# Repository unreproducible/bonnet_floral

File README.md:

Floral Bonnet

This is an IoT-ish style Bonnet (Hat) intended for a Raspberry Pi Zero based board.

Obviously you can use it on anything with the appropriate header.

Includes:
* BME280 - I2C
* TSL2561 - I2C
* 128x64 OLED Screen - SPI
* RGB LED - 3xGPIO/PWM
* User Button - GPIO
* Serial Port for Kernel Debugging

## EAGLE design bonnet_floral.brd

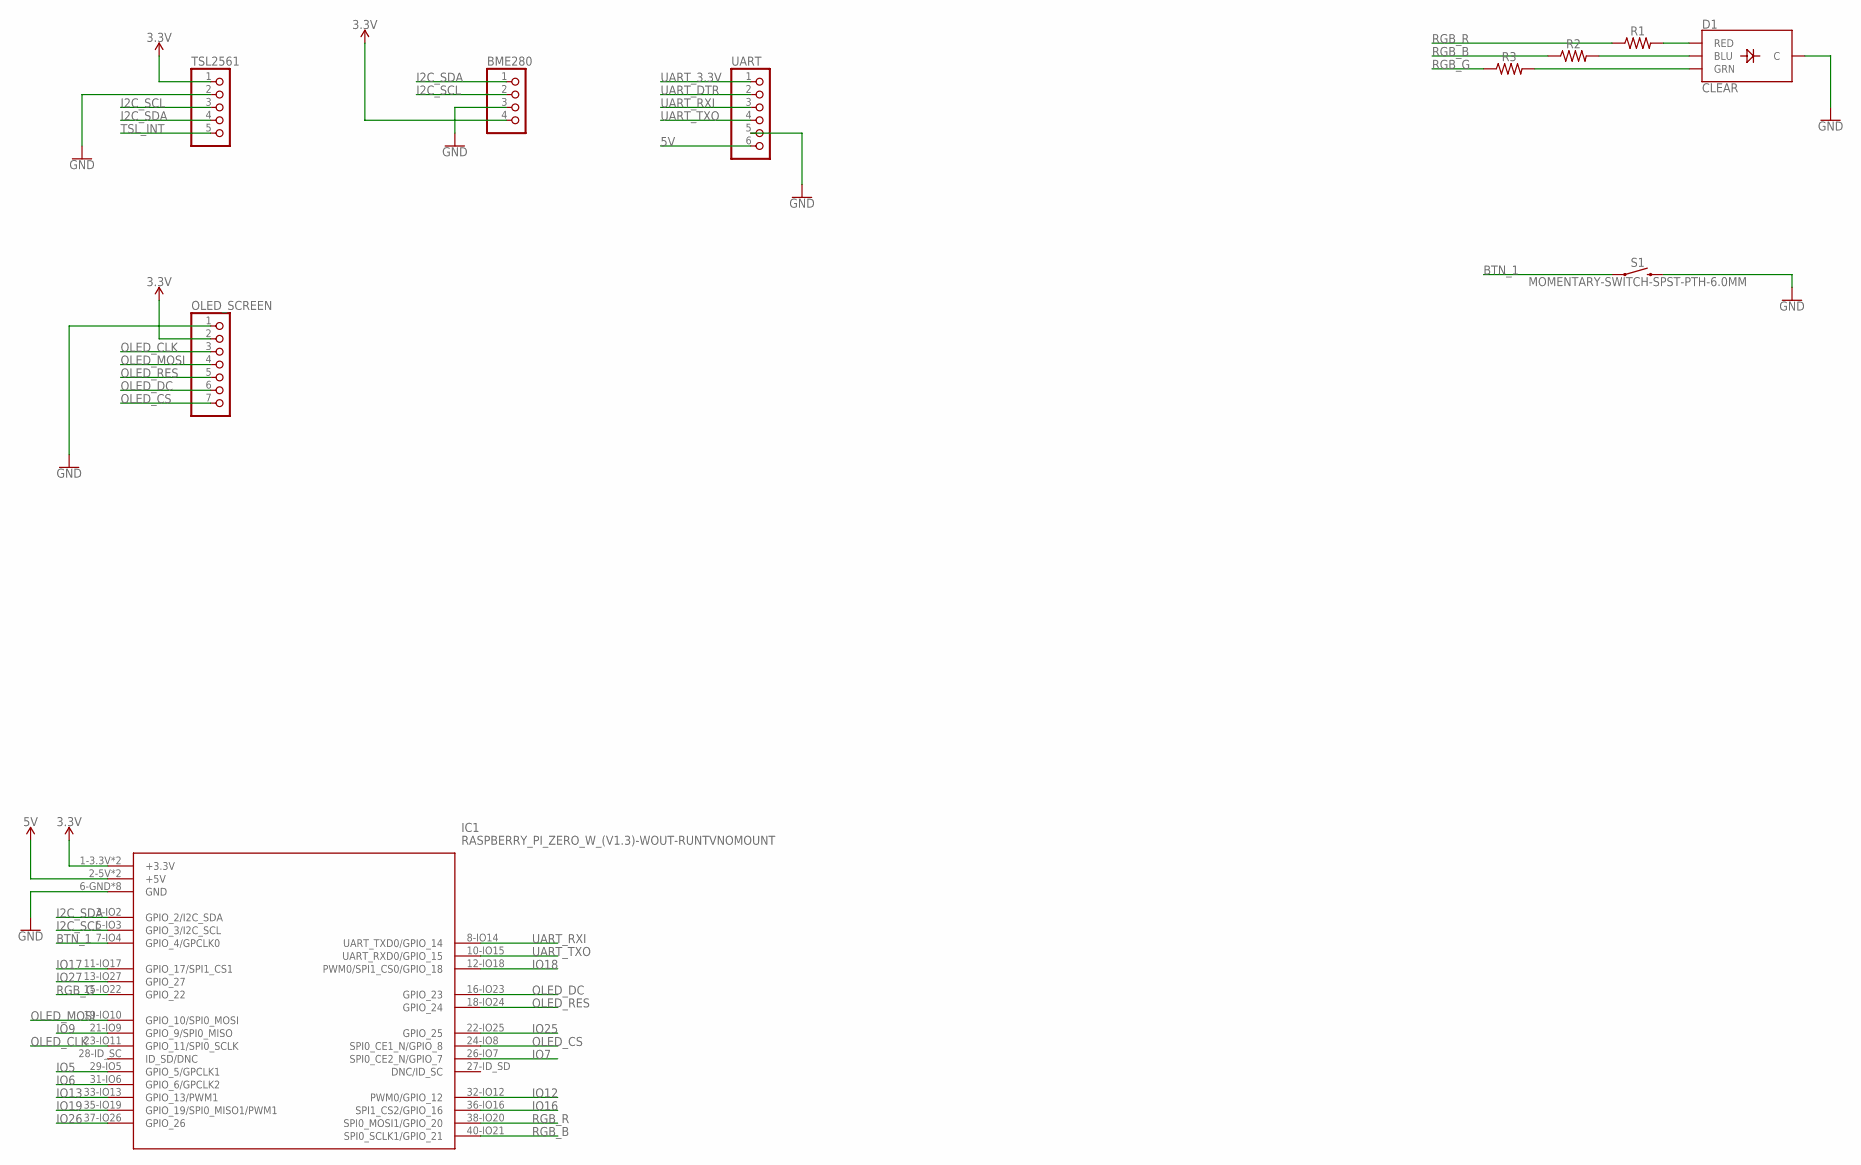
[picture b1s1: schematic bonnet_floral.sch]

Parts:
BME280: PINHD-1X4; 1X04
D1: CLEAR; LED-RGB-THRU@1
IC1: RASPBERRY_PI_ZERO_W_(V1.3)-WOUT-RUNTVNOMOUNT; RASPBERRYPIZEROWV13-WOUT-RUNTV-NOMOUNT
OLED_SCREEN: PINHD-1X7; 1X07
R1, R2, R3: AXIAL-0.3
S1: MOMENTARY-SWITCH-SPST-PTH-6.0MM; TACTILE_SWITCH_PTH_6.0MM
TSL2561: PINHD-1X5; 1X05
UART: PINHD-1X6; 1X06

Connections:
3.3V: BME280.4, IC1.1-3.3V (+3.3V), IC1.17-3.3V (+3.3V), OLED_SCREEN.2, TSL2561.1
5V: IC1.2-5V (+5V), IC1.4-5V (+5V), UART.6
BTN_1: IC1.7-IO4 (GPIO_4/GPCLK0), S1.1
GND: BME280.3, D1.2 (C), IC1.6-GND (GND), IC1.9-GND (GND), IC1.14-GND (GND), IC1.20-GND (GND), IC1.25-GND (GND), IC1.30-GND (GND), IC1.34-GND (GND), IC1.39-GND (GND), OLED_SCREEN.1, S1.3 (2), TSL2561.2, UART.5
I2C_SCL: BME280.2, IC1.5-IO3 (GPIO_3/I2C_SCL), TSL2561.3
I2C_SDA: BME280.1, IC1.3-IO2 (GPIO_2/I2C_SDA), TSL2561.4
IO5: IC1.29-IO5 (GPIO_5/GPCLK1)
IO6: IC1.31-IO6 (GPIO_6/GPCLK2)
IO7: IC1.26-IO7 (SPI0_CE2_N/GPIO_7)
IO9: IC1.21-IO9 (GPIO_9/SPI0_MISO)
IO12: IC1.32-IO12 (PWM0/GPIO_12)
IO13: IC1.33-IO13 (GPIO_13/PWM1)
IO16: IC1.36-IO16 (SPI1_CS2/GPIO_16)
IO17: IC1.11-IO17 (GPIO_17/SPI1_CS1)
IO18: IC1.12-IO18 (PWM0/SPI1_CS0/GPIO_18)
IO19: IC1.35-IO19 (GPIO_19/SPI0_MISO1/PWM1)
IO25: IC1.22-IO25 (GPIO_25)
IO26: IC1.37-IO26 (GPIO_26)
IO27: IC1.13-IO27 (GPIO_27)
unnamed: D1.1 (RED), R1.P$2 (2)
unnamed: D1.4 (BLU), R2.P$2 (2)
unnamed: D1.3 (GRN), R3.P$2 (2)
OLED_CLK: IC1.23-IO11 (GPIO_11/SPI0_SCLK), OLED_SCREEN.3
OLED_CS: IC1.24-IO8 (SPI0_CE1_N/GPIO_8), OLED_SCREEN.7
OLED_DC: IC1.16-IO23 (GPIO_23), OLED_SCREEN.6
OLED_MOSI: IC1.19-IO10 (GPIO_10/SPI0_MOSI), OLED_SCREEN.4
OLED_RES: IC1.18-IO24 (GPIO_24), OLED_SCREEN.5
RGB_B: IC1.40-IO21 (SPI0_SCLK1/GPIO_21), R2.P$1 (1)
RGB_G: IC1.15-IO22 (GPIO_22), R3.P$1 (1)
RGB_R: IC1.38-IO20 (SPI0_MOSI1/GPIO_20), R1.P$1 (1)
TSL_INT: TSL2561.5
UART_3.3V: UART.1
UART_DTR: UART.2
UART_RXI: IC1.8-IO14 (UART_TXD0/GPIO_14), UART.3
UART_TXO: IC1.10-IO15 (UART_RXD0/GPIO_15), UART.4

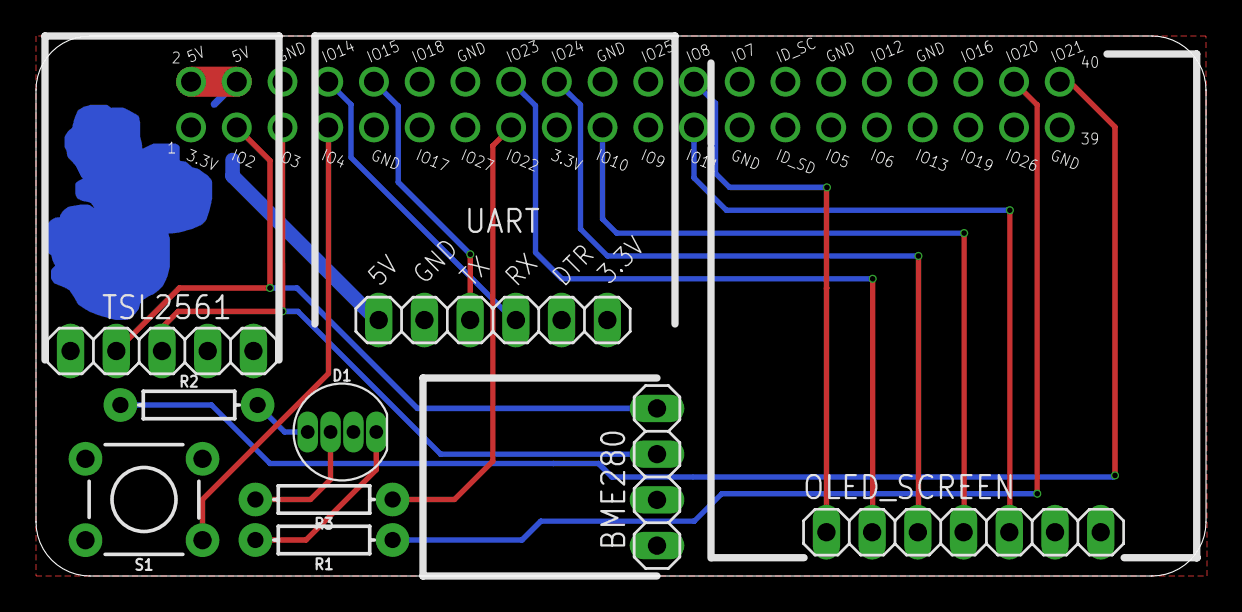
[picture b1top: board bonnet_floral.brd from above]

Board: 2 copper layers, 65.0 x 30.0 mm, 11 parts (1 on the bottom side), 19 nets.

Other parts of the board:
U$1: FLORAL_SMALLER_MIRROR

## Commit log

2018-11-03 Initial Commit - Basic Board Template
2018-11-03 Adding V0.9 of the Floral Bonnet
    This completes all the major pieces, it's rough but basically
    ready to be shipped out for prototyping
2018-11-03 Adding Schematic PDF and board image
2018-11-03 Adding Prototype (v0.9) gerbers
2018-11-06 UART was rotate 180deg the wrong direction. Rotated correctly
    I've added pinout information for it as well so it's slightly
    more obvious what's going on
2018-11-07 Reving the board version number to 0.9.1
    This is a bugfix version release, the changes aren't finalized
    but figured reving the version now would mean it's done when we
    run the next set of prototypes
2018-11-08 Moving the BME280 down a little
    The BME280 was right up against the lower side of the CP2102, so
    I'm moving it down 1mm (and re-routing the signals as needed) to
    give it a little bit of space.
2018-11-08 Adjusting the back silkscreen, adding artwork
    Also cleaning up the DRC checks from before
2018-11-08 Adding Artwork used
2018-11-08 More adjustments to the silk/artwork
2018-11-08 Committing Gerbers v0.9.1 - bugfix release, tagging
2018-11-08 Adjusting the back silkscreen, adding artwork to board
    Also cleaning up the DRC checks from before
    removing https:// from the board url to make it bigger
2019-01-14 Initial README.md file added
2019-01-14 Adding the last of the production materials
    These are mostly used if you are going to do a full production run
    of the bonnets. That being said they may be found useful to someone
    who is doing their own assembly as well.
2021-05-08 Moving the Gerbers zip around so it's easier to distinguish
2021-05-08 Adjusting silkscreen post LCA
    So this is basically going to open it up for general usage. I'm
    going to keep the original v0.9.1 as "special" for LCA 2019, and
    not continue with that identifier in v0.9.2 (the changes are purely
    cosmetic)
2021-05-08 Updating gerbers, revving to version 0.9.2
2021-05-08 Adjusting silkscreen post LCA
    So this is basically going to open it up for general usage. I'm
    going to keep the original v0.9.1 as "special" for LCA 2019, and
    not continue with that identifier in v1.0 (the changes are purely
    cosmetic)
2021-05-08 Updating gerbers, revving to version v1.0
2021-05-10 Add Example / Test code
    This is the code that was used to verify the functionality of the Floral
    Bonnet. You'll need a few external repositories to fully test
    everything (and submodules seems like a mess to do for something this
    simple). Just run gitclone.sh and snag the respective repositories.
    To see how things are run take a look at commands.txt
2021-05-12 Add starlight commands & BME280 & TSL2561 driver
    This pulls in the drivers for the BME280 and the TSL2561 directly
    instead of relying on the upstream location, particularly since they
    haven't been updated since 2018, and the license is compatible here.
    This also adds in basic commands to get everything working on the
    BeagleV Starlight board which has a compatible 2x20 pin header.
    Currently the luma examples are disabled as trying to get the SSD1306
2022-10-17 Add Serial Port 5V power feed
    So in the original design the power coming from the serial port header
    was intentionally left N/C, however there's argument that this might
    have made some learning applications more complicated / expensive.
    Attaching it to the main PI header 5V looks like it should work, and
    feed into the same 5V linke the normal power header does. Since the 5V
    coming from the serial port chip seems to also feed directly from the
2022-10-17 Rev board to v1.1
2022-10-17 Gerbers: update to v1.1
2022-10-17 Rev schematic to v1.1
2022-10-17 Rotate oled screen 90deg counter-clockwise
    This is basically a manufacturing optimization to move the under side
    components of the oled screen away from the pi header. There's a cap
    that comes a bit close to the header and it's troublesome. This shifts
    the screen around and allows for just some kapton tape on the oled
    screen to alleviate any possible touching / arcing.

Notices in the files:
bonnet_floral.brd:
(C) 2021 CC-BY-SA 4.0
parts and their libraries:
SparkFun-LED: Licensing: Creative Commons ShareAlike 4.0 International - https://creativecommons.org/licenses/by-sa/4.0
